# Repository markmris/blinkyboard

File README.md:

# Blinky Board / 555 LED Chaser

This is my first hardware project I made for Hack Club's Stasis event. It's a classic 555 LED chaser that lights up LEDs in a set sequence at a set speed. I made it following the beginner project guide.

## Custom Feature
I added a pause button that stops the LEDs from rotating when held down and continues when the button is let go.

## Schematic
The schematic design was my first step, and the spot where I felt the most lost. It felt like I was thrown into the cockpit of a plane and was just told what to click without knowing what it actually does. I took it really slowly, however, and I constantly asked my Stasis sidekick questions, dropped a few in the #stasis channel and got Claude and ChatGPT to explain a few things, and I started getting familiar with it! About a day or two later I was finished with my schematic prepared with my own feature.

## PCB
The second step was the PCB design. This part was also confusing, but not as before since I now knew what each circuit did and just did my best with following the beginner guide. I kept falling down the rabbit hole of routes getting in the way of each other and not being able to finish until a long time later, I learnt that I had 2 layers I could route on, which made this thousands of times easier. I used much less AI while making the PCB and would just search up something like a keyboard shortcut to make my life easier, but the biggest help was the lock in call I joined where I learnt a lot from the people in there and saved myself lots of pain and suffering. From that call I learnt about fill zones and how to use vias for grounding.

## 3D Render
After finally finishing the PCB I then added my signature near the bottom (Mark. M). It felt really rewarding to look at the render, and it felt even better that the Design Rules Check passed on the first try.

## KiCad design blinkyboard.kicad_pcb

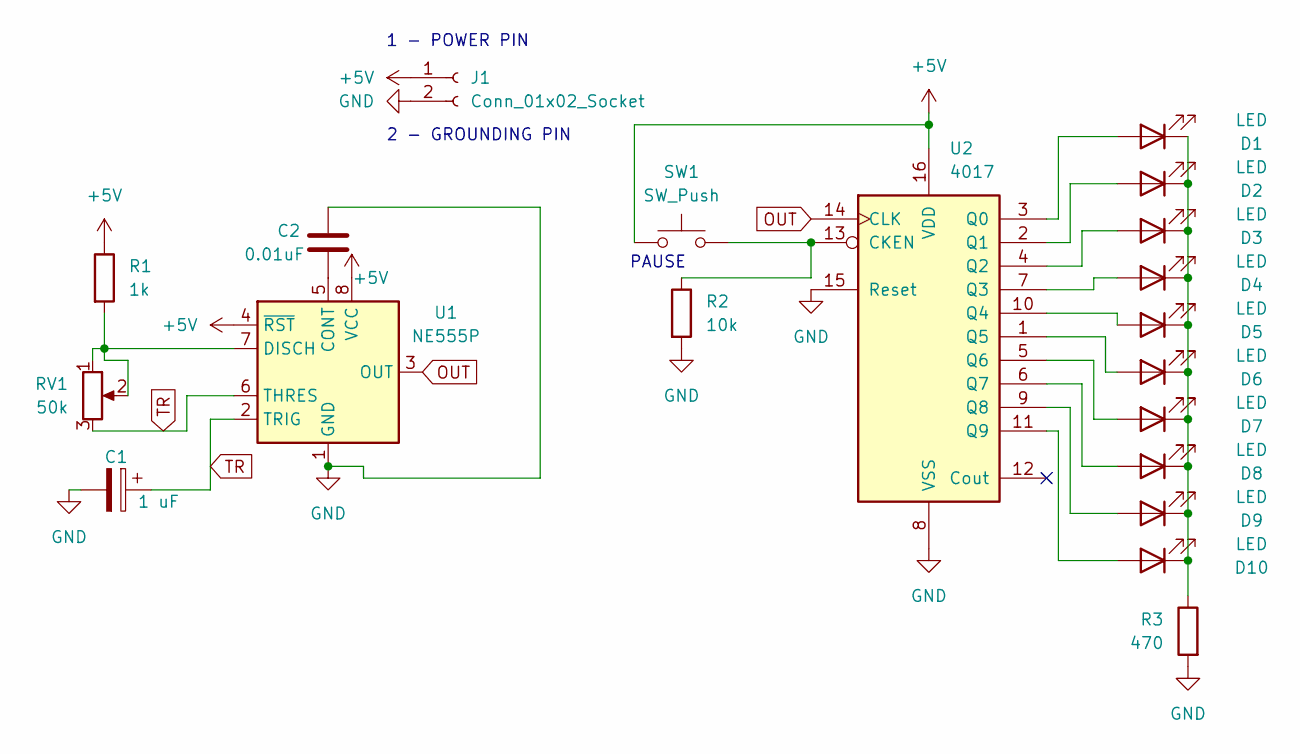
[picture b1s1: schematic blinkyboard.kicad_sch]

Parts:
C1: 1 uF; CP_Radial_D5.0mm_P2.50mm
C2: 0.01uF; C_Disc_D5.0mm_W2.5mm_P5.00mm
D1, D2, D3, D4, D5, D6, D7, D8, D9, D10: LED; LED_D5.0mm
J1: Conn_01x02_Socket; PinHeader_1x02_P2.54mm_Vertical
R1: 1k; R_Axial_DIN0207_L6.3mm_D2.5mm_P10.16mm_Horizontal
R2: 10k; R_Axial_DIN0207_L6.3mm_D2.5mm_P10.16mm_Horizontal
R3: 470; R_Axial_DIN0207_L6.3mm_D2.5mm_P10.16mm_Horizontal
RV1: 50k; Potentiometer_Bourns_3386P_Vertical
SW1: SW_Push; SW_PUSH_6mm
U1: NE555P; DIP-8_W7.62mm
U2: 4017; N16

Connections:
+5V: J1.1, R1.1, SW1.1, U1.4 (~RST), U1.8 (VCC), U2.16 (VDD)
GND: C1.2, C2.1, J1.2, R2.2, R3.2, U1.1 (GND), U2.8 (VSS), U2.15 (Reset)
unnamed: D1.2 (A), U2.3 (Q0)
unnamed: D1.1 (K), D2.1 (K), D3.1 (K), D4.1 (K), D5.1 (K), D6.1 (K), D7.1 (K), D8.1 (K), D9.1 (K), D10.1 (K), R3.1
unnamed: D2.2 (A), U2.2 (Q1)
unnamed: D3.2 (A), U2.4 (Q2)
unnamed: D4.2 (A), U2.7 (Q3)
unnamed: D5.2 (A), U2.10 (Q4)
unnamed: D6.2 (A), U2.1 (Q5)
unnamed: D7.2 (A), U2.5 (Q6)
unnamed: D8.2 (A), U2.6 (Q7)
unnamed: D9.2 (A), U2.9 (Q8)
unnamed: D10.2 (A), U2.11 (Q9)
unnamed: C2.2, U1.5 (CONT)
unnamed: R1.2, RV1.1, RV1.2, U1.7 (DISCH)
unnamed: R2.1, SW1.2, U2.13 (CKEN)
OUT: U1.3 (OUT), U2.14 (CLK)
TR: C1.1, RV1.3, U1.2 (TRIG), U1.6 (THRES)

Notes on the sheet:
1 - POWER PIN
2 - GROUNDING PIN
PAUSE

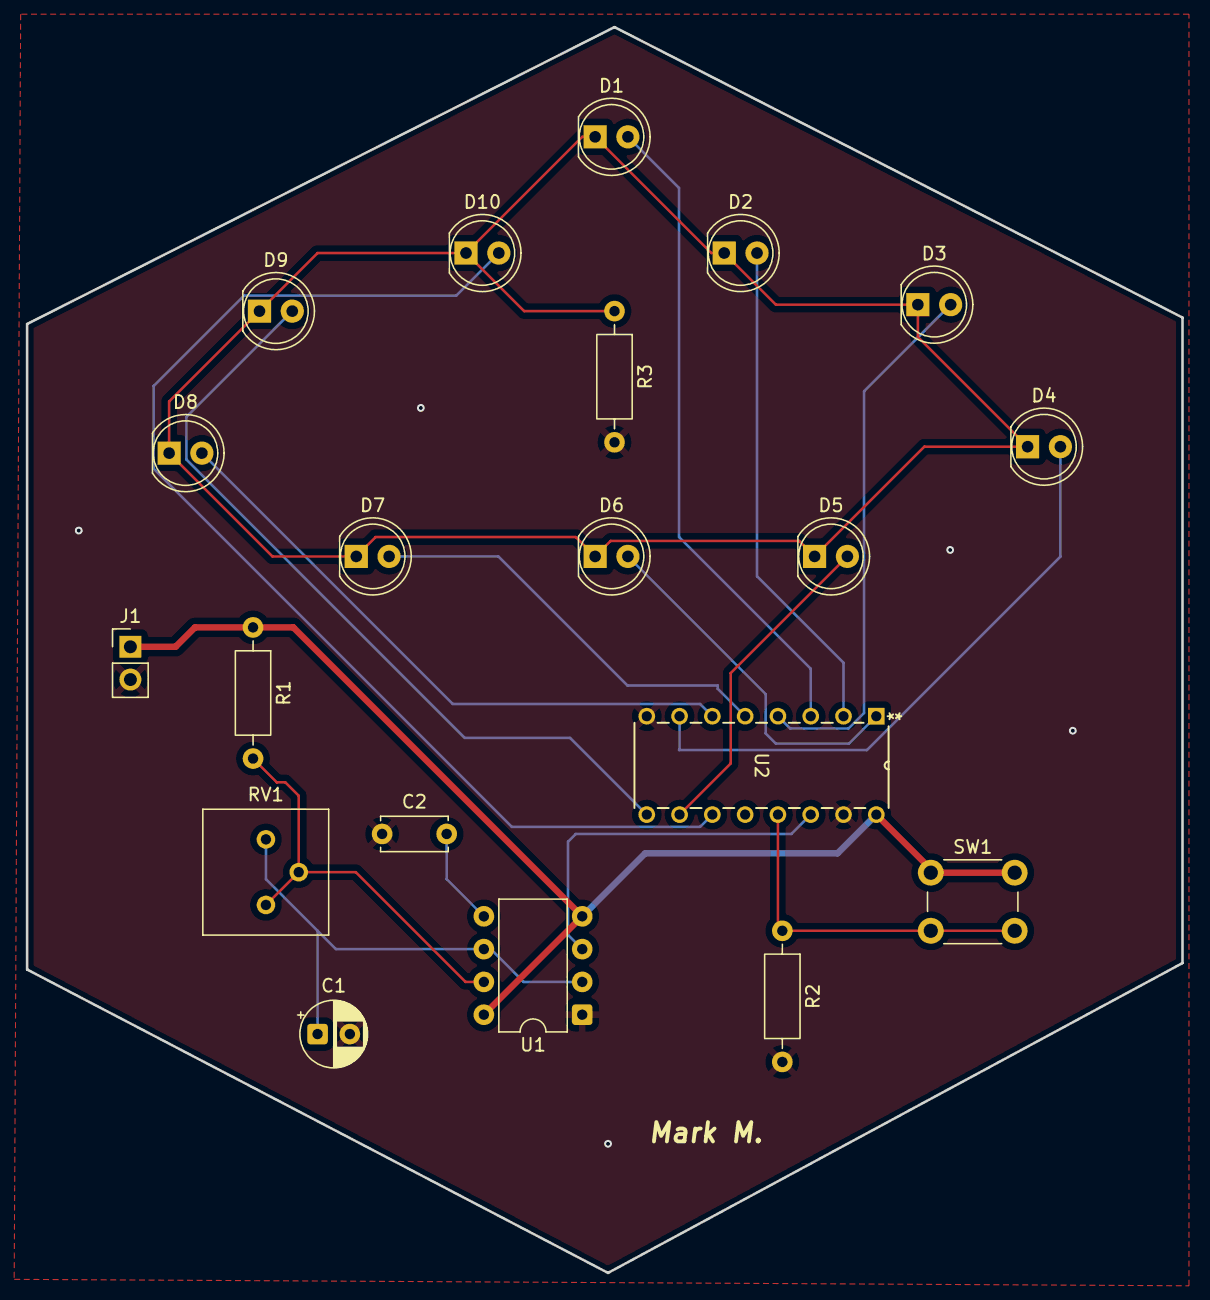
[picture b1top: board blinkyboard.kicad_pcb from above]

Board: 2 copper layers, 89.5 x 96.5 mm, 20 parts (0 on the bottom side), 18 nets.

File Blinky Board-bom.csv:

Name,Purpose,Quantity,Total Cost (USD),Link,Distributor
"Resistors","Slows current so LEDs flash properly and help NE555P time properly",1,0.99,"https://www.aliexpress.us/item/2251832831152798.html?spm=a2g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","AliExpress"
"3386P Potentiometer","Helps the NE555 time properly",1,0.99,"https://www.aliexpress.us/item/3256807296452484.html?spm=a2g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","AliExpress"
"SW Push Button","Button that pauses the light sequence",1,0.99,"https://www.aliexpress.us/item/3256808606199192.html?spm=a2g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","AliExpress"
"0.01uF Capacitor","Helps the NE555P time properly",1,0.99,"https://www.aliexpress.us/item/3256810257090517.html?spm=a2g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","AliExpress"
"1uF Polarized Capacitor","Helps the NE555P time properly",1,0.99,"https://www.aliexpress.us/item/3256801889213205.html?spm=a2g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","AliExpress"
"2x1 2.54mm Conn Pin Header","Pin Header for power and grounding",1,0.99,"https://www.aliexpress.us/item/3256808907494688.html?spm=a2g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","AliExpress"
"CD4017","IO Expander to flash LEDs",1,0.99,"https://www.aliexpress.us/item/3256804346585931.html?spm=a2g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","AliExpress"
"THT LEDs","The LED lights for the chaser",1,0.99,"https://www.aliexpress.us/item/2251801072728213.html?spm=a2g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","AliExpress"
"NE555P","Counts sequences for when each LED should flash",1,0.99,"https://www.aliexpress.us/item/3256808526542898.html?spm=a2g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","AliExpress"

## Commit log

2026-03-18 Add KiCad project files (Not finished)
2026-03-18 Upload updated schematic
2026-03-18 Update schematic
2026-03-20 Final update for KiCad files.
2026-03-20 Add 3D render of PCB
2026-03-20 Import gerbers
2026-03-20 Add Readme
2026-03-20 Readd 3D render
2026-03-20 Update Readme
    Expanded project description and added sections on custom features, schematic, PCB design, and 3D render.
2026-03-23 Upload BOM
2026-03-23 Update BOM
2026-03-23 Reupload BOM
